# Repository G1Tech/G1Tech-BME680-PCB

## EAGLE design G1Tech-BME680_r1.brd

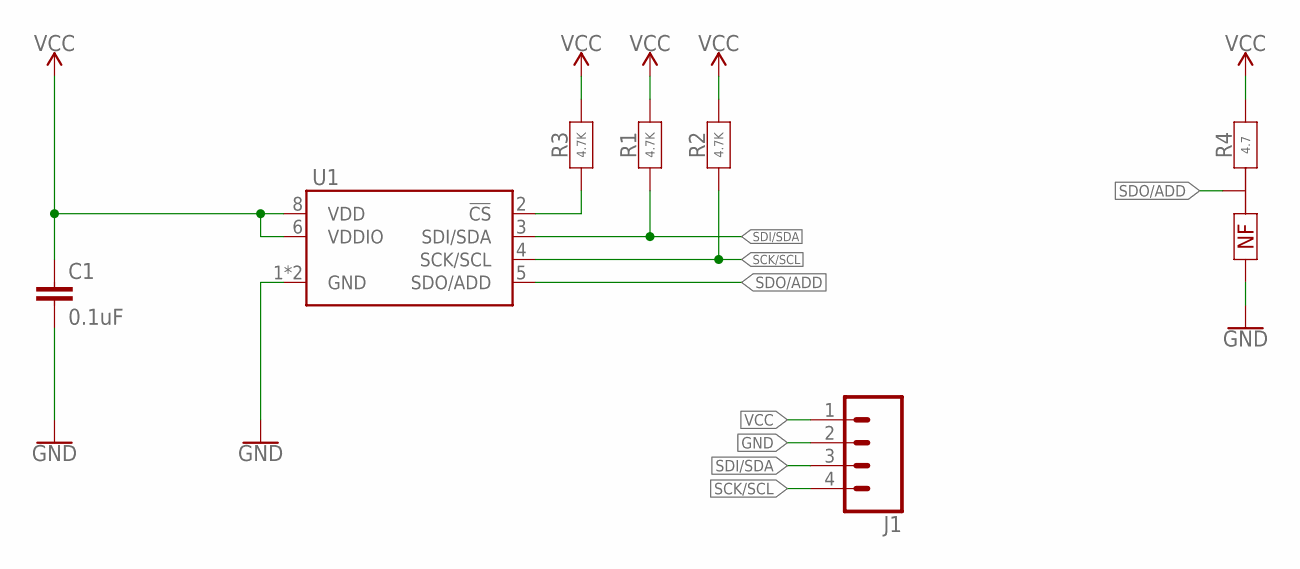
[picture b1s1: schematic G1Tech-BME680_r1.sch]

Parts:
C1: 0.1uF; TDK-C0603
J1: CONN_04; 1X04
R1, R2, R3: 4.7K; YAGEO-R0603
R4: 4.7; YAGEO-JP0603
U1: BOSH-BME680

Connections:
!CS: R3.1, U1.2 (!CS)
GND: C1.2, J1.2, R4.3, U1.1 (GND), U1.7 (GND)
SCK/SCL: J1.4, R2.1, U1.4 (SCK/SCL)
SDI/SDA: J1.3, R1.1, U1.3 (SDI/SDA)
SDO/ADD: R4.2, U1.5 (SDO/ADD)
VCC: C1.1, J1.1, R1.2, R2.2, R3.2, R4.1, U1.6 (VDDIO), U1.8 (VDD)

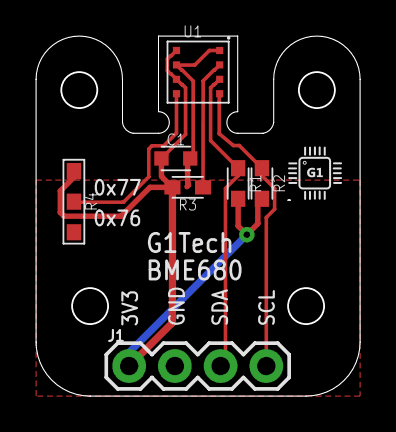
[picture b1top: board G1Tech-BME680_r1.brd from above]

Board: 2 copper layers, 17.9 x 19.9 mm, 9 parts (1 on the bottom side), 6 nets.

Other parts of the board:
U$1, U$2: LOGO-G1TECH-3MM

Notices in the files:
parts and their libraries:
SparkFun-Connectors: Licensing: Creative Commons ShareAlike 4.0 International - https://creativecommons.org/licenses/by-sa/4.0
